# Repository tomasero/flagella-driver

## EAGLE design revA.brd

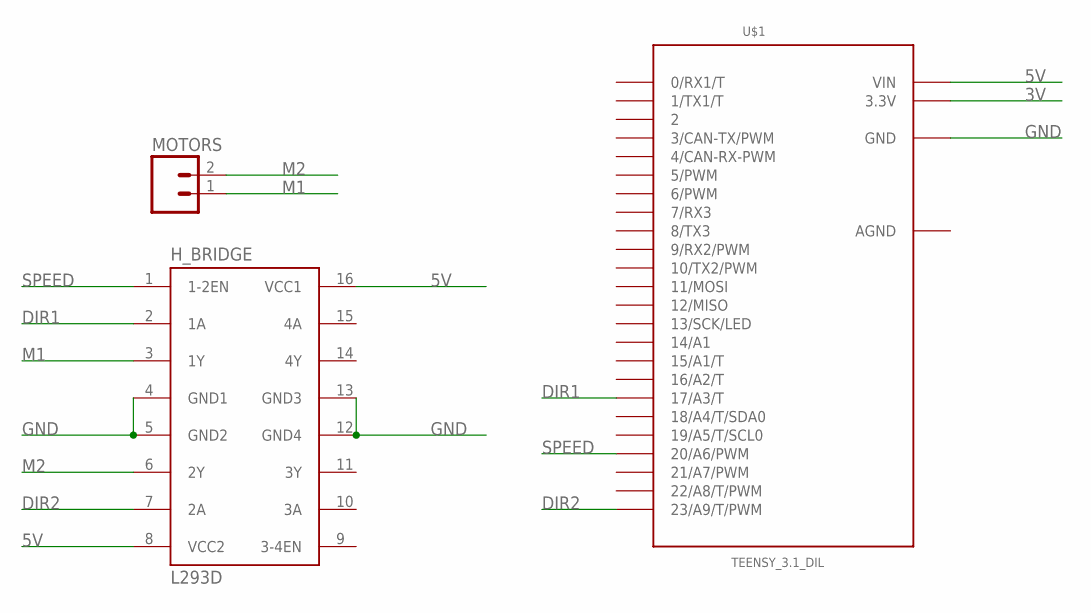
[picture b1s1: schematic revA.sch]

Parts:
H_BRIDGE: L293D; DIL16
MOTORS: M02JST-PTH-2; JST-2-PTH
U$1: TEENSY_3.1_DIL; TEENSY3-DIL

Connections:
3V: U$1.3.3V
5V: H_BRIDGE.8 (VCC2), H_BRIDGE.16 (VCC1), U$1.VIN
AGND: U$1.AGND
DIR1: H_BRIDGE.2 (1A), U$1.17/A3 (17/A3/T)
DIR2: H_BRIDGE.7 (2A), U$1.23/A9 (23/A9/T/PWM)
GND: H_BRIDGE.4 (GND1), H_BRIDGE.5 (GND2), H_BRIDGE.12 (GND4), H_BRIDGE.13 (GND3), U$1.GND
M1: H_BRIDGE.3 (1Y), MOTORS.1
M2: H_BRIDGE.6 (2Y), MOTORS.2
SPEED: H_BRIDGE.1 (1-2EN), U$1.20/A6 (20/A6/PWM)

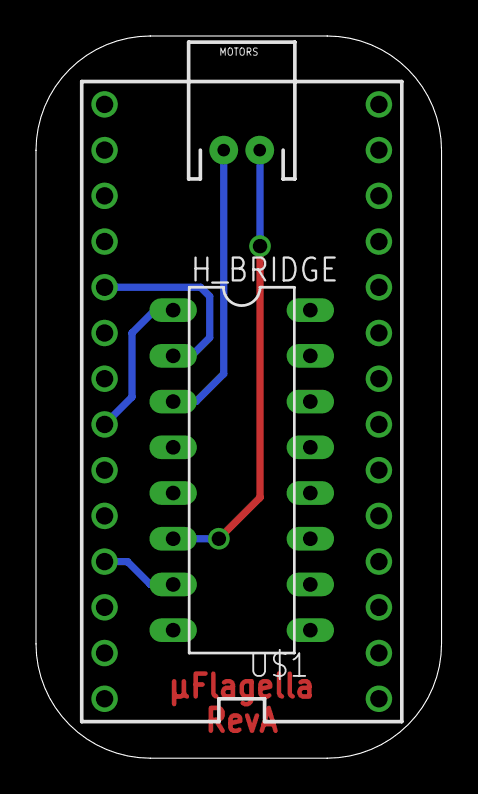
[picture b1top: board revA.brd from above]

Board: 2 copper layers, 22.5 x 40.1 mm, 3 parts (0 on the bottom side), 7 nets.

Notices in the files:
parts and their libraries:
SparkFun-Connectors: Licensing: Creative Commons ShareAlike 4.0 International - https://creativecommons.org/licenses/by-sa/4.0
